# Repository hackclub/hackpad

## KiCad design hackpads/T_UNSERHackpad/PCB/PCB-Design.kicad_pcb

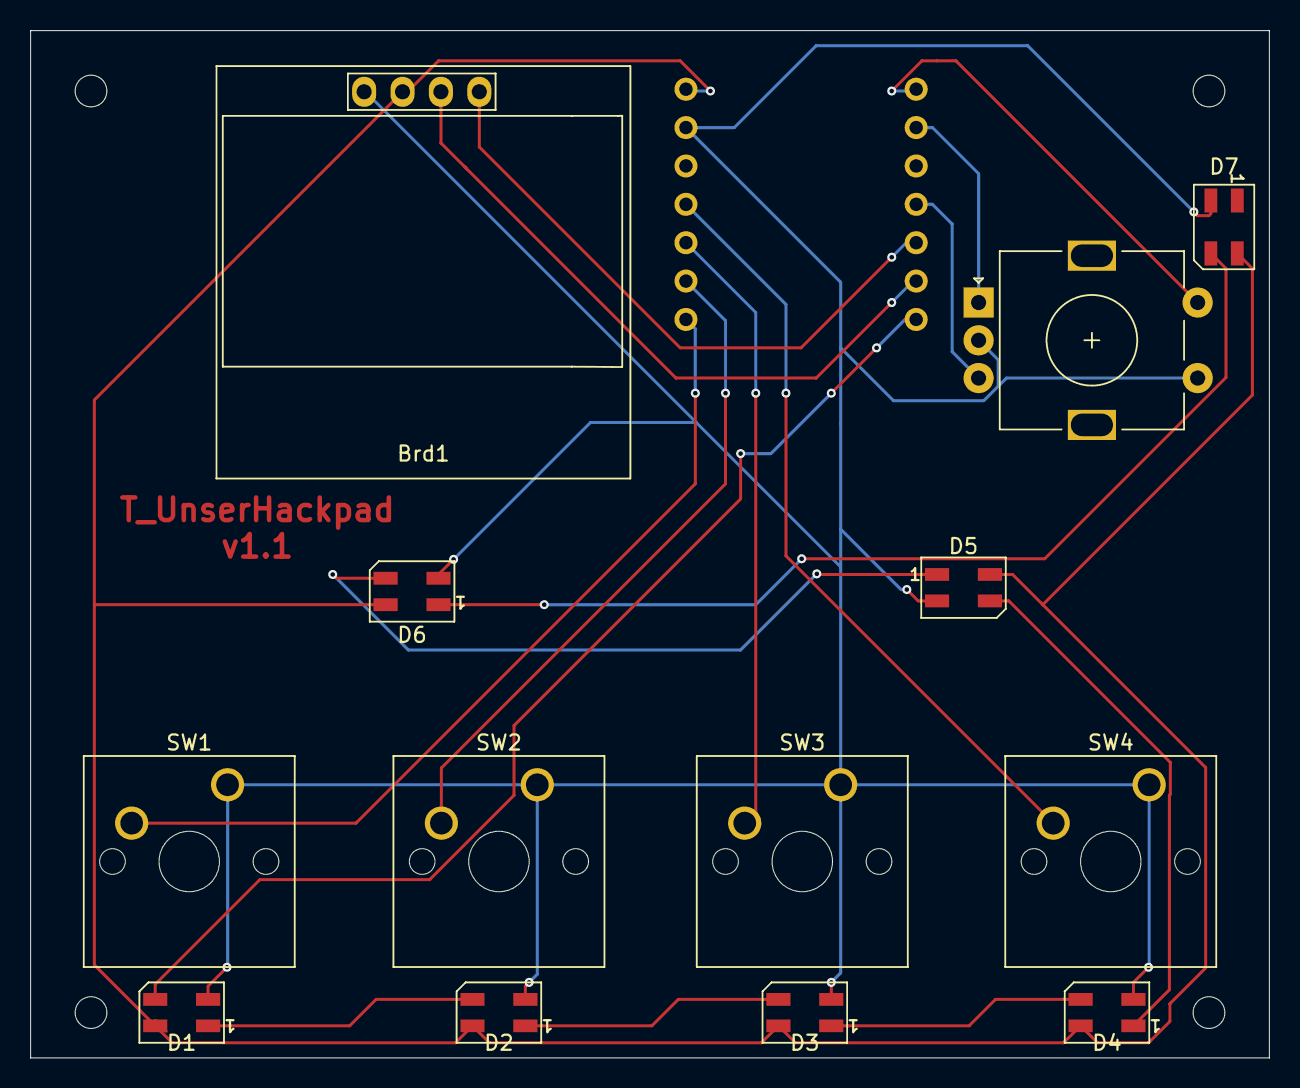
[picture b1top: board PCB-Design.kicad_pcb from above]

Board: 2 copper layers, 82.0 x 68.0 mm, 14 parts (1 on the bottom side), 18 nets.

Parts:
Brd1: SSD1306; 128x64OLED
D1, D2, D3, D4, D5, D6, D7: SK6812MINI; LED_SK6812MINI_PLCC4_3.5x3.5mm_P1.75mm
SW1, SW2, SW3, SW4: SW_Push; SW_Cherry_MX_1.00u_PCB
SW5: RotaryEncoder_Switch; RotaryEncoder_Alps_EC11E-Switch_Vertical_H20mm
U1: XIAO-RP2040-DIP

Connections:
+5V: Brd1.2 (VCC), D1.4 (VDD), D2.4 (VDD), D3.4 (VDD), D4.4 (VDD), D5.4 (VDD), D6.4 (VDD), D7.4 (VDD), U1.14 (VBUS)
GND: Brd1.1 (GND), D1.2 (VSS), D2.2 (VSS), D3.2 (VSS), D4.2 (VSS), D5.2 (VSS), D6.2 (VSS), D7.2 (VSS), SW1.1, SW2.1, SW3.1, SW4.1, SW5.C, SW5.S1, U1.13 (GND)
unnamed: Brd1.3 (SCL), U1.6 (GPIO7/SCL)
unnamed: Brd1.4 (SDA), U1.5 (GPIO6/SDA)
unnamed: D1.3 (DIN), U1.7 (GPIO0/TX)
unnamed: D1.1 (DOUT), D2.3 (DIN)
unnamed: D2.1 (DOUT), D3.3 (DIN)
unnamed: D3.1 (DOUT), D4.3 (DIN)
unnamed: D4.1 (DOUT), D5.3 (DIN)
unnamed: D5.1 (DOUT), D6.3 (DIN)
unnamed: D6.1 (DOUT), D7.3 (DIN)
unnamed: SW1.2, U1.8 (GPIO1/RX)
unnamed: SW2.2, U1.9 (GPIO2/SCK)
unnamed: SW4.2, U1.11 (GPIO3/MOSI)
unnamed: SW3.2, U1.10 (GPIO4/MISO)
unnamed: SW5.S2, U1.1 (GPIO26/ADC0/A0)
unnamed: SW5.A, U1.2 (GPIO27/ADC1/A1)
unnamed: SW5.B, U1.4 (GPIO29/ADC3/A3)

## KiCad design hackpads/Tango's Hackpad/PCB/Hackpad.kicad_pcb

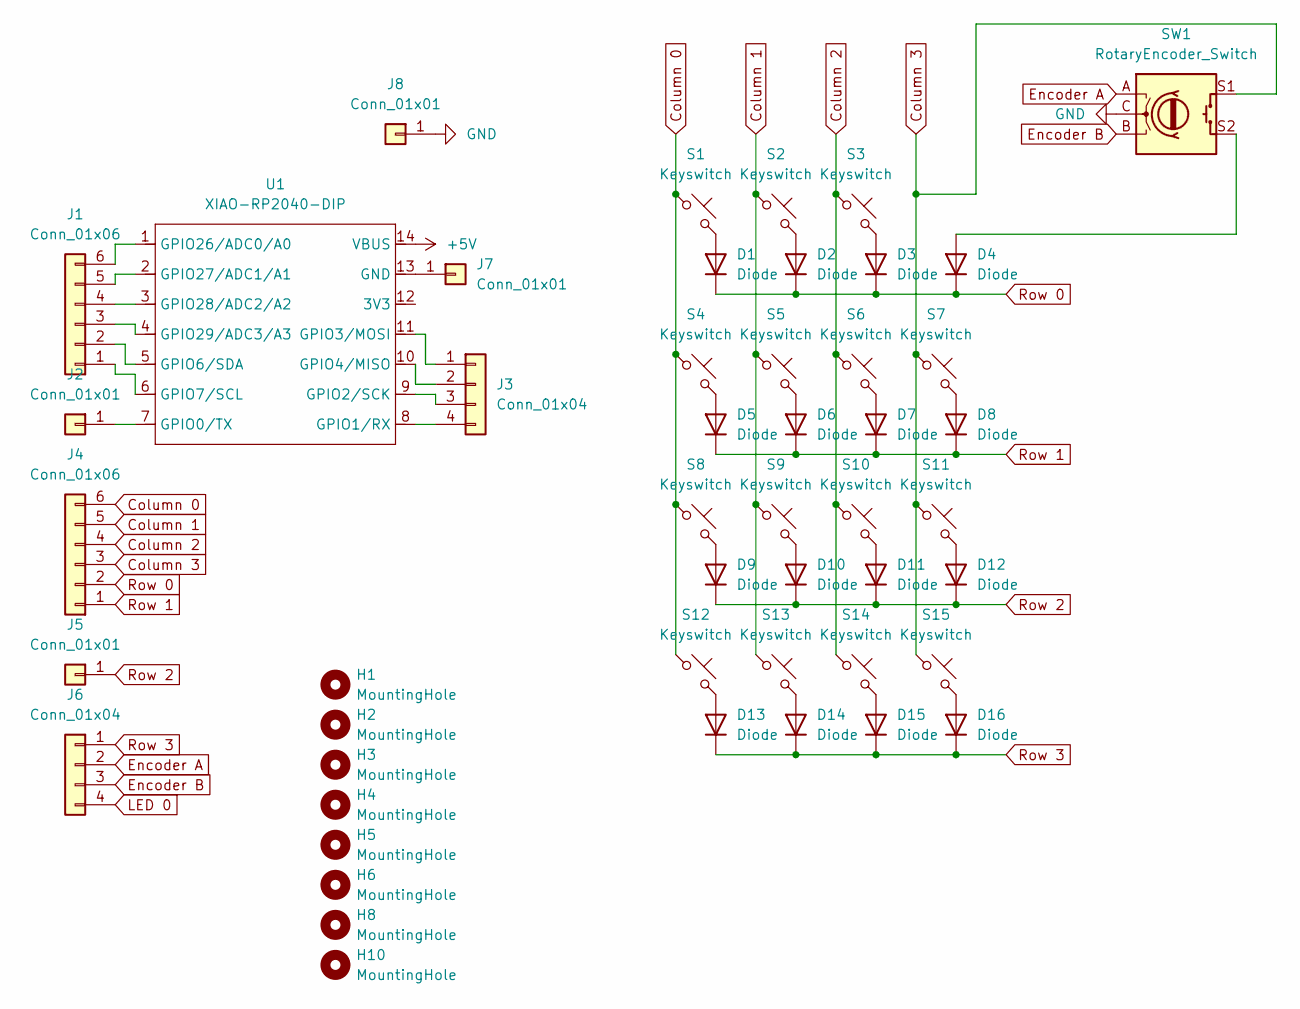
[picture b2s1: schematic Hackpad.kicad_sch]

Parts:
D1, D2, D3, D4, D5, D6, D7, D8, D9, D10, D11, D12, D13, D14, D15, D16: Diode; Diode_DO-35
H1, H2, H3, H4, H5, H6, H8, H10: MountingHole; MountingHole_2.2mm_M2_DIN965_Pad
J1, J4: Conn_01x06; SolderWire-0.1sqmm_1x06_P3.6mm_D0.4mm_OD1mm
J2, J5, J7, J8: Conn_01x01; SolderWire-0.1sqmm_1x01_D0.4mm_OD1mm
J3, J6: Conn_01x04; SolderWire-0.1sqmm_1x04_P3.6mm_D0.4mm_OD1mm
S1, S2, S3, S4, S5, S6, S7, S8, S9, S10, S11, S12, S13, S14, S15: Keyswitch; MX_PCB_1.00u
SW1: RotaryEncoder_Switch; RotaryEncoder_Alps_EC11E-Switch_Vertical_H20mm
U1: XIAO-RP2040-DIP

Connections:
+5V: U1.14 (VBUS)
Column 0: J4.6, S1.1, S4.1, S8.1, S12.1
Column 1: J4.5, S2.1, S5.1, S9.1, S13.1
Column 2: J4.4, S3.1, S6.1, S10.1, S14.1
Column 3: J4.3, S7.1, S11.1, S15.1, SW1.S1
Encoder A: J6.2, SW1.A
Encoder B: J6.3, SW1.B
GND: J8.1, SW1.C
LED 0: J6.4
unnamed: D1.2 (A), S1.2
unnamed: D2.2 (A), S2.2
unnamed: D3.2 (A), S3.2
unnamed: D4.2 (A), SW1.S2
unnamed: D5.2 (A), S4.2
unnamed: D6.2 (A), S5.2
unnamed: D7.2 (A), S6.2
unnamed: D8.2 (A), S7.2
unnamed: D9.2 (A), S8.2
unnamed: D10.2 (A), S9.2
unnamed: D11.2 (A), S10.2
unnamed: D12.2 (A), S11.2
unnamed: D13.2 (A), S12.2
unnamed: D14.2 (A), S13.2
unnamed: D15.2 (A), S14.2
unnamed: D16.2 (A), S15.2
unnamed: J1.1, U1.6 (GPIO7/SCL)
unnamed: J1.2, U1.5 (GPIO6/SDA)
unnamed: J1.3, U1.4 (GPIO29/ADC3/A3)
unnamed: J1.4, U1.3 (GPIO28/ADC2/A2)
unnamed: J1.5, U1.2 (GPIO27/ADC1/A1)
unnamed: J1.6, U1.1 (GPIO26/ADC0/A0)
unnamed: J2.1, U1.7 (GPIO0/TX)
unnamed: J3.1, U1.11 (GPIO3/MOSI)
unnamed: J3.2, U1.10 (GPIO4/MISO)
unnamed: J3.3, U1.9 (GPIO2/SCK)
unnamed: J3.4, U1.8 (GPIO1/RX)
unnamed: J7.1, U1.13 (GND)
Row 0: D1.1 (K), D2.1 (K), D3.1 (K), D4.1 (K), J4.2
Row 1: D5.1 (K), D6.1 (K), D7.1 (K), D8.1 (K), J4.1
Row 2: D9.1 (K), D10.1 (K), D11.1 (K), D12.1 (K), J5.1
Row 3: D13.1 (K), D14.1 (K), D15.1 (K), D16.1 (K), J6.1

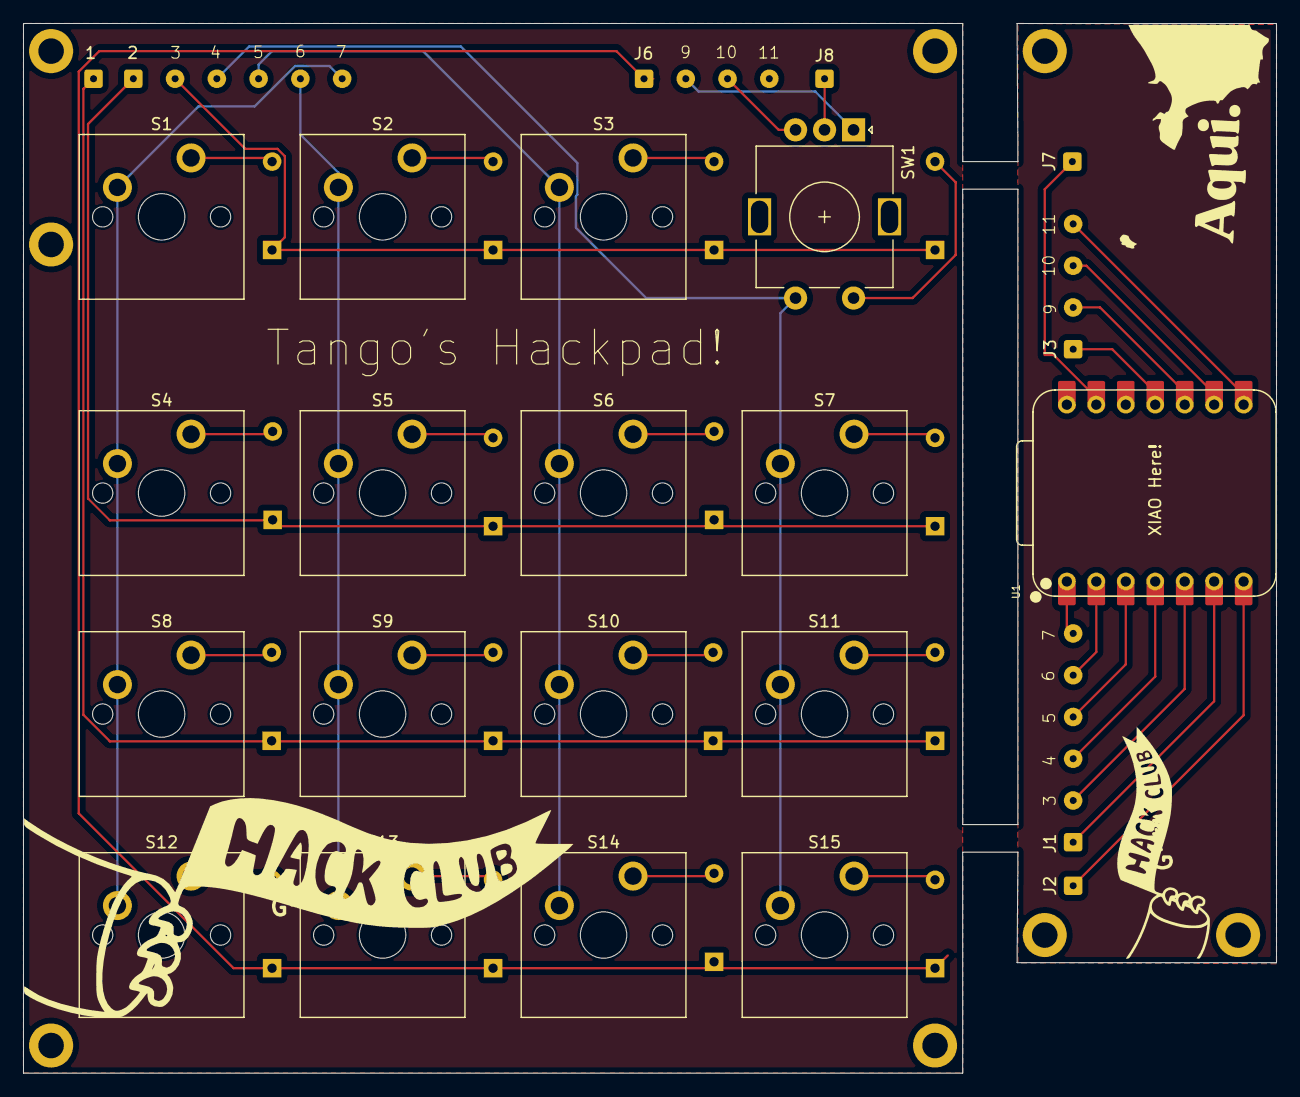
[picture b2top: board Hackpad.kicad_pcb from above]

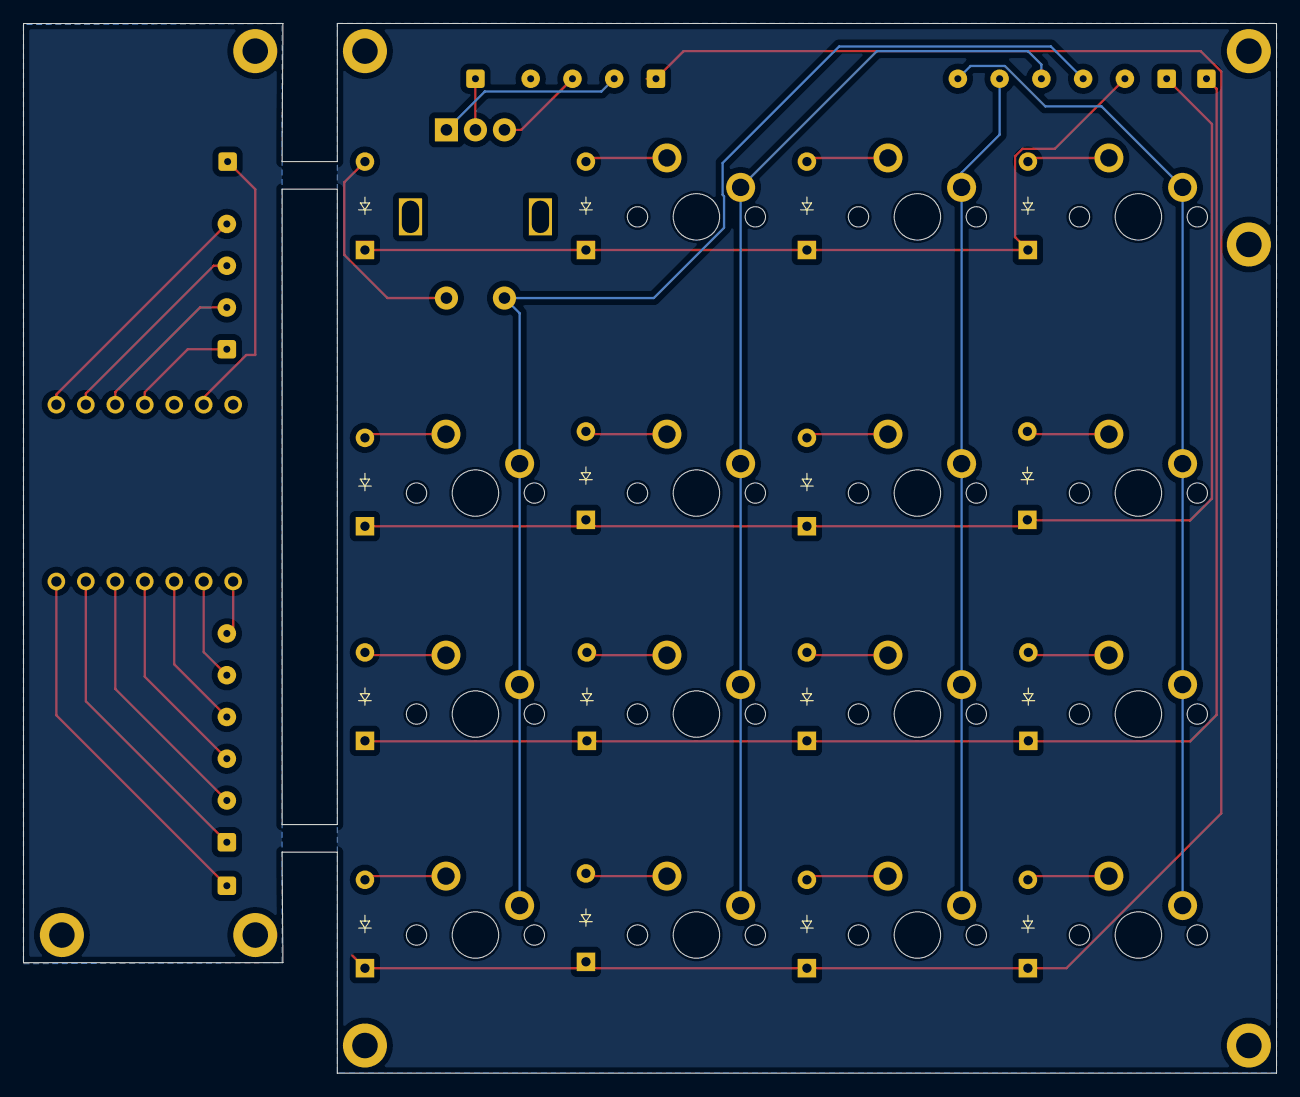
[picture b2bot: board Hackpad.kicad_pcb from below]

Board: 2 copper layers, 108.0 x 90.5 mm, 49 parts (16 on the bottom side), 39 nets.

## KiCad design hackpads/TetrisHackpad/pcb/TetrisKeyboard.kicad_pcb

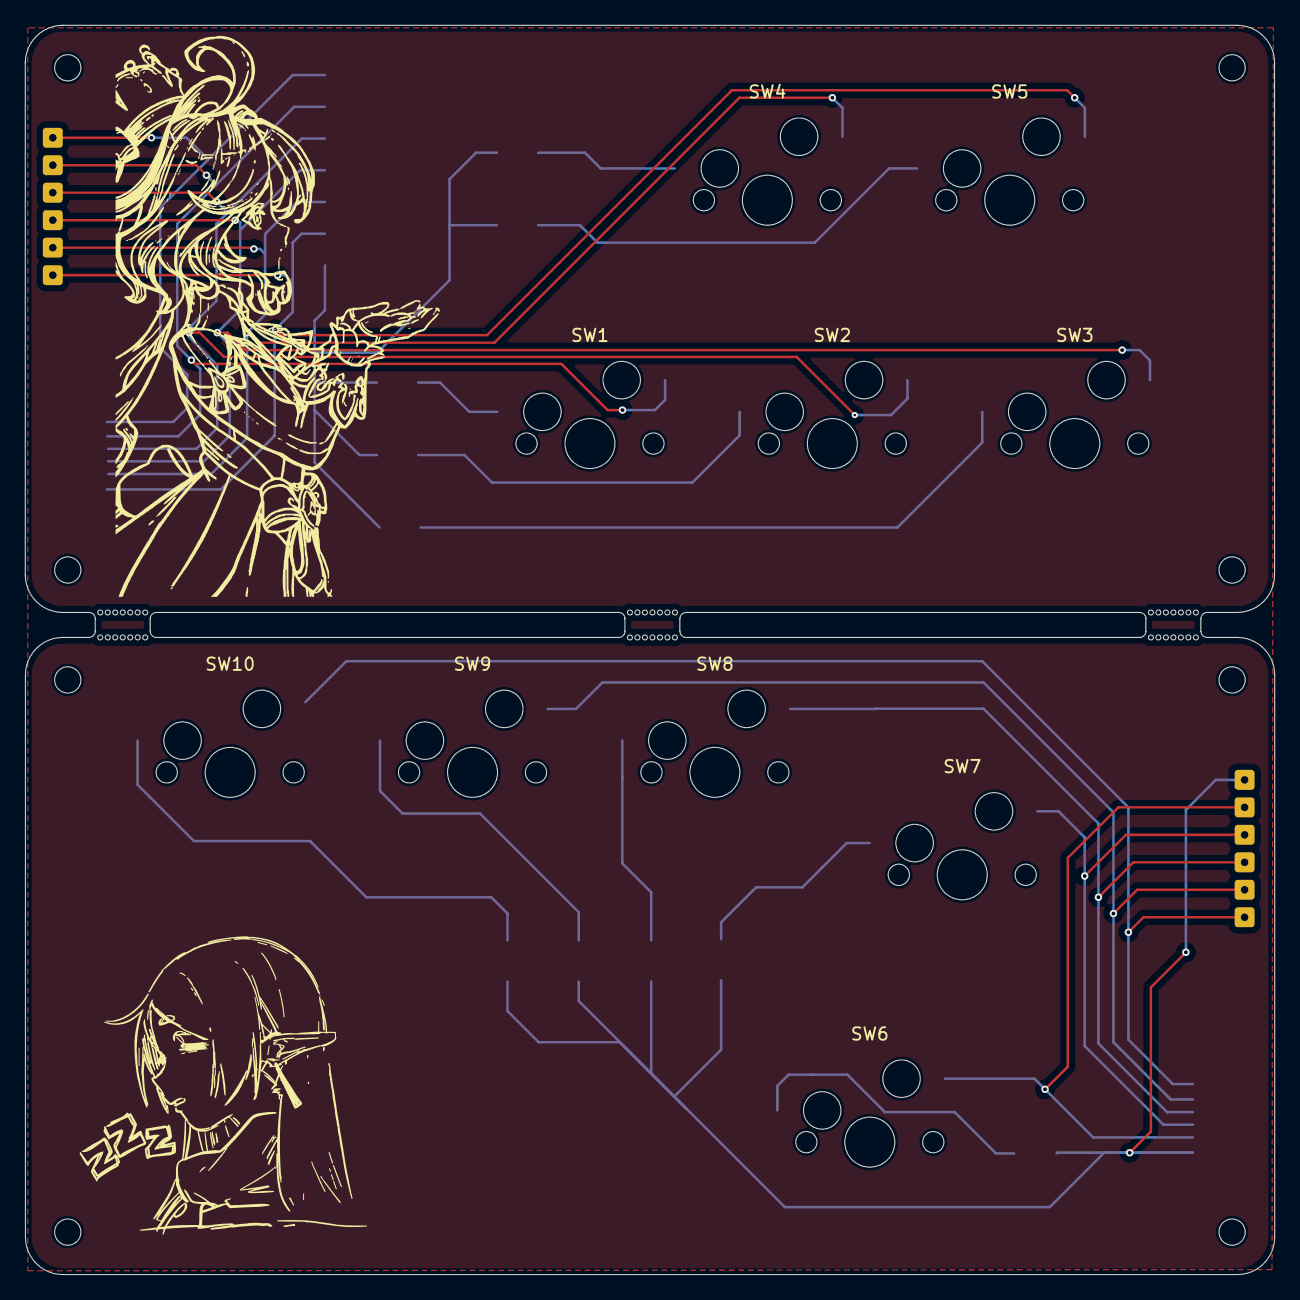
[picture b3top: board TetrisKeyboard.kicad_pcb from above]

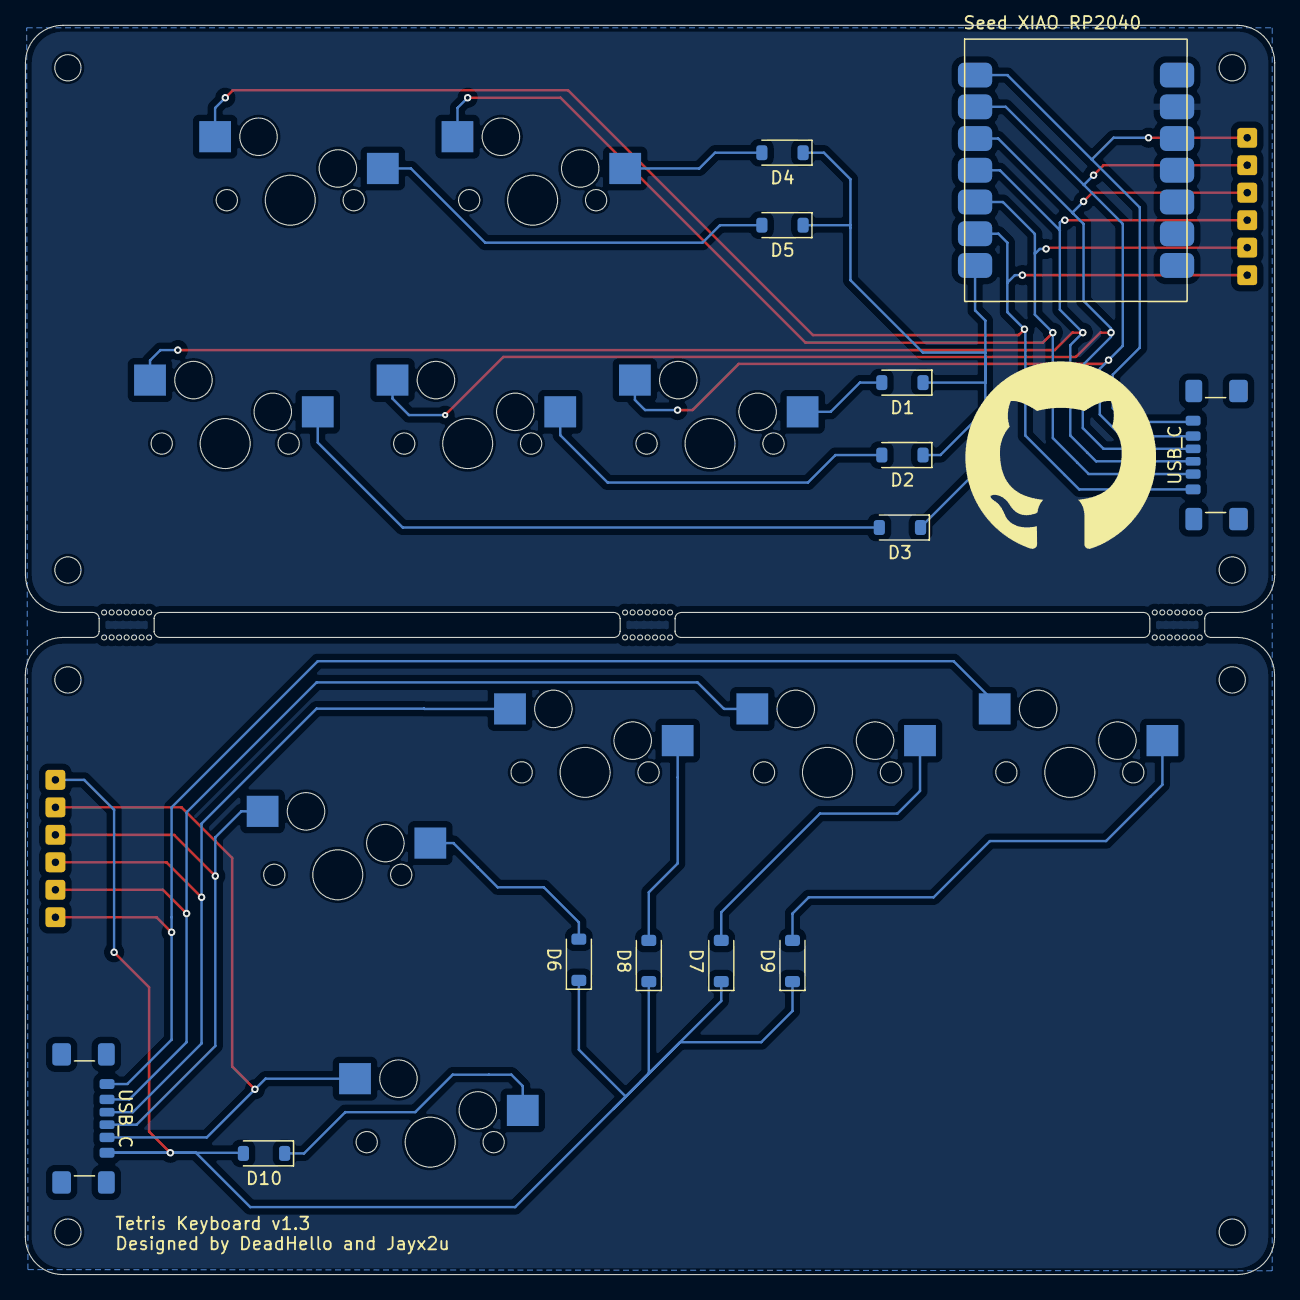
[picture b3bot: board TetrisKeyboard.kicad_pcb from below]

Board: 2 copper layers, 100.0 x 100.0 mm, 30 parts (13 on the bottom side), 13 nets.

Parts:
2.1mm, 2.1mm#2, 2.1mm#3, 2.1mm#4, 2.1mm#5, 2.1mm#6: MountingHole_2.1mm
D1, D2, D3, D4, D5, D6, D7, D8, D9, D10: 1N4148W; D_SOD-123
NO: LOGO
SW1, SW2, SW3, SW4, SW5, SW6, SW7, SW8, SW9, SW10: CherryMX_1.00u_KailhSocket
Seed XIAO RP2040: MOUDLE14P-SMD-2.54-21X17.8MM
USB_C: USB_C_Receptacle_GCT_USB4135-GF-A_6P_TopMnt_Horiz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; USB_C_Receptacle_GCT_USB4135-GF-A_6P_TopMnt_Horizontal
USB_C#2: USB_C_Receptacle_GCT_USB4135-GF-A_6P_TopMnt_Horiz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; USB_C_Receptacle_GCT_USB4135-GF-A_6P_TopMnt_Horizontal

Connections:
Col1: SW1.2, Seed XIAO RP2040.2, USB_C.A9
Col1-B: SW6.2, USB_C#2.A9
Col2: SW2.2, Seed XIAO RP2040.3, USB_C.B5
Col2-B: SW7.2, USB_C#2.B5
Col3: SW3.2, Seed XIAO RP2040.4, USB_C.A5
Col3-B: SW8.2, USB_C#2.A5
Col4: SW4.2, Seed XIAO RP2040.5, USB_C.B9
Col4-B: SW9.2, USB_C#2.B9
Col5: SW5.2, Seed XIAO RP2040.6, USB_C.B12
Col5-B: SW10.2, USB_C#2.B12
Row1: D1.1, D1.2, D2.1, D2.2, D3.1, D3.2, D4.1, D4.2, D5.1, D5.2, SW1.1, SW2.1, SW3.1, SW4.1, SW5.1, Seed XIAO RP2040.7
Row2: Seed XIAO RP2040.1, USB_C.A12
Row2-B: D6.1, D6.2, D7.1, D7.2, D8.1, D8.2, D9.1, D9.2, D10.1, D10.2, SW6.1, SW7.1, SW8.1, SW9.1, SW10.1, USB_C#2.A12

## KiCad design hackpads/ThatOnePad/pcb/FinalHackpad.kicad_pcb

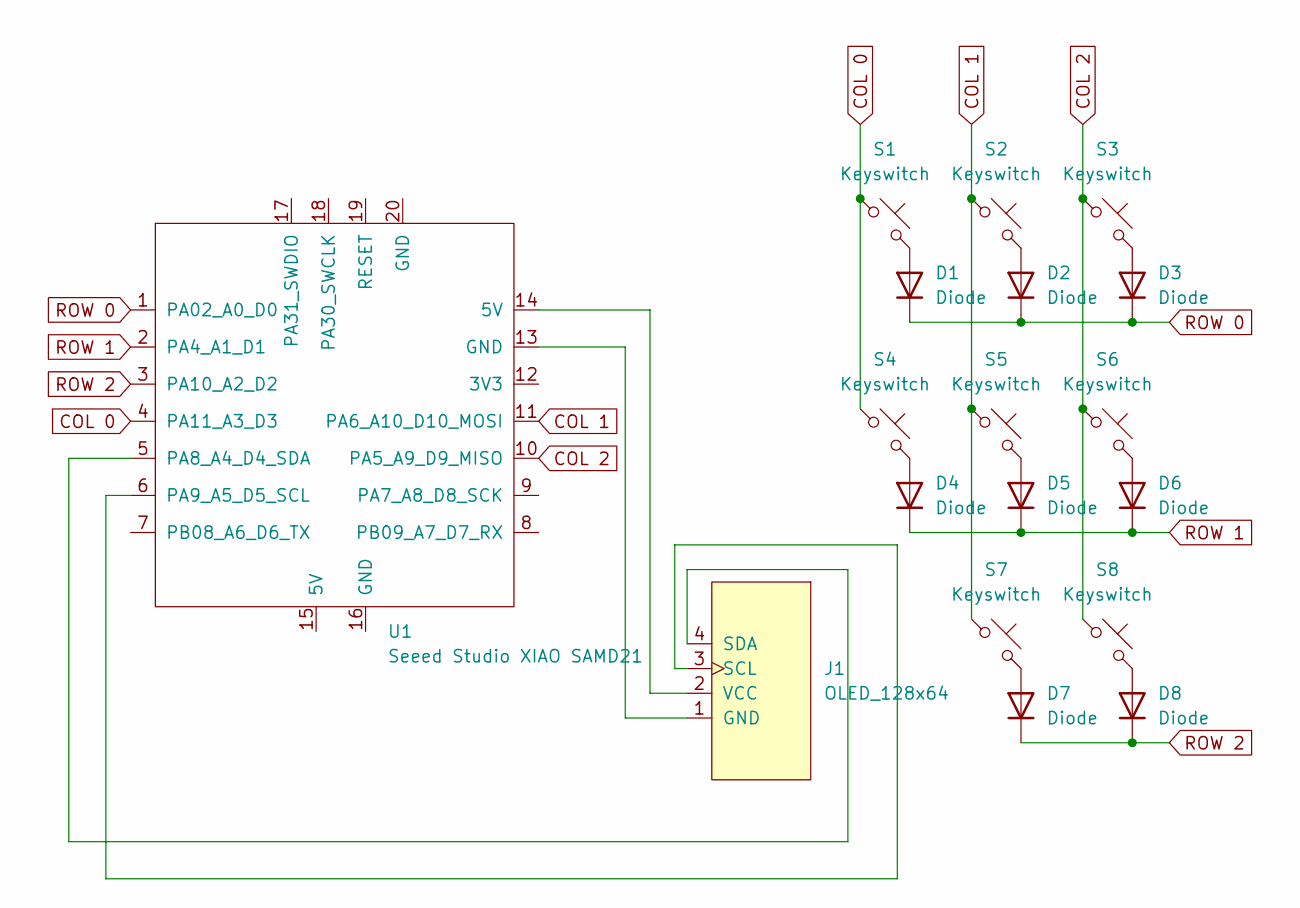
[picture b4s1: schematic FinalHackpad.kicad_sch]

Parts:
D1, D2, D3, D4, D5, D6, D7, D8: Diode; Diode_DO-35
J1: OLED_128x64
S1, S2, S3, S4, S5, S6, S7, S8: Keyswitch; SW_Cherry_MX_1.00u_PCB
U1: Seeed Studio XIAO SAMD21; Seeed_XIAO_RP2040

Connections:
COL 0: S1.1, S4.1, U1.4 (PA11_A3_D3)
COL 1: S2.1, S5.1, S7.1, U1.11 (PA6_A10_D10_MOSI)
COL 2: S3.1, S6.1, S8.1, U1.10 (PA5_A9_D9_MISO)
unnamed: D1.2 (A), S1.2
unnamed: D2.2 (A), S2.2
unnamed: D3.2 (A), S3.2
unnamed: D4.2 (A), S4.2
unnamed: D5.2 (A), S5.2
unnamed: D6.2 (A), S6.2
unnamed: D7.2 (A), S7.2
unnamed: D8.2 (A), S8.2
unnamed: J1.1 (GND), U1.13 (GND)
unnamed: J1.3 (SCL), U1.6 (PA9_A5_D5_SCL)
unnamed: J1.4 (SDA), U1.5 (PA8_A4_D4_SDA)
unnamed: J1.2 (VCC), U1.14 (5V)
ROW 0: D1.1 (K), D2.1 (K), D3.1 (K), U1.1 (PA02_A0_D0)
ROW 1: D4.1 (K), D5.1 (K), D6.1 (K), U1.2 (PA4_A1_D1)
ROW 2: D7.1 (K), D8.1 (K), U1.3 (PA10_A2_D2)

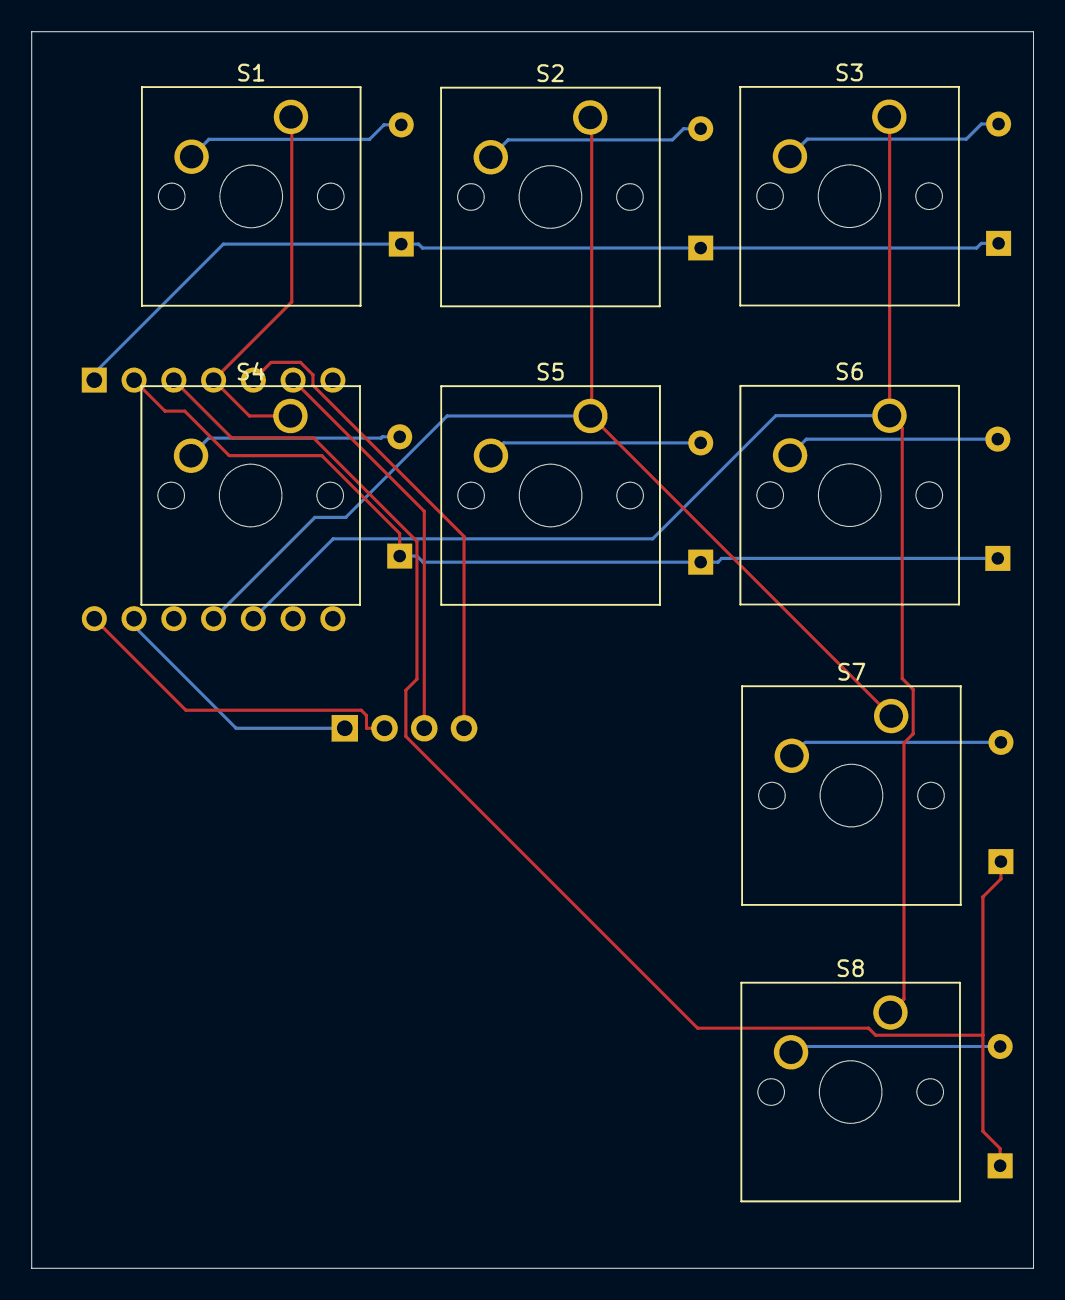
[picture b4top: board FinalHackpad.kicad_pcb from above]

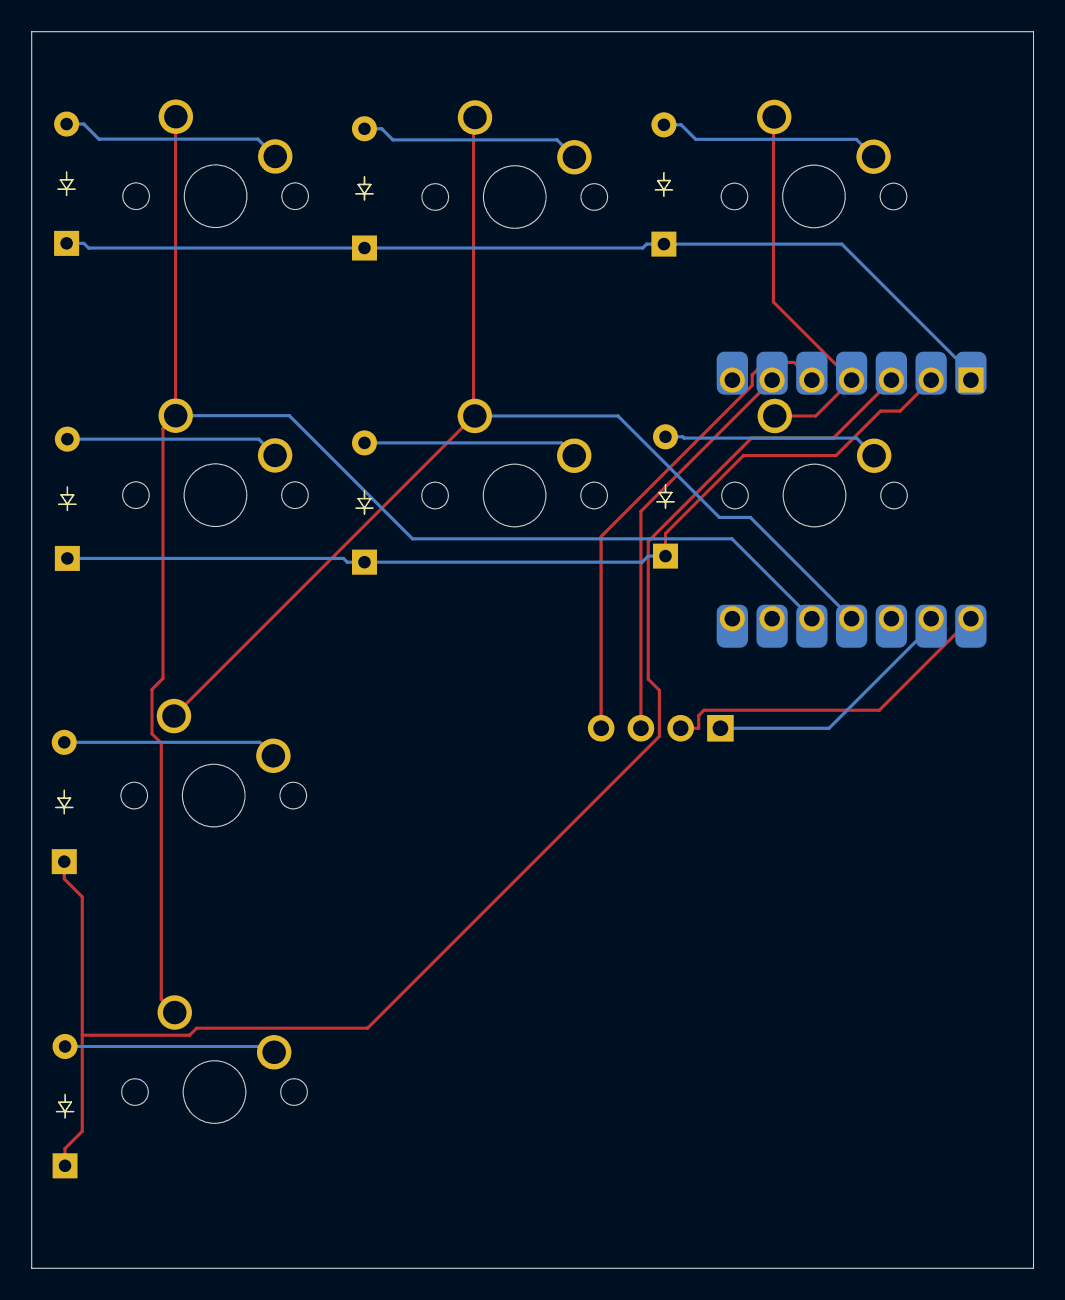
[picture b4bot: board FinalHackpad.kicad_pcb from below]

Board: 2 copper layers, 64.0 x 79.0 mm, 18 parts (9 on the bottom side), 18 nets.

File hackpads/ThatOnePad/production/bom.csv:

Designator,Footprint,Quantity,Value,LCSC Part #
"D1, D2, D3, D4, D5, D6, D7, D8",Diode_DO-35,8,Diode,
J1,OLED_128x64,1,OLED_128x64,
"S1, S2, S3, S4, S5, S6, S7, S8",SW_Cherry_MX_1.00u_PCB,8,Keyswitch,
U1,Seeed_XIAO_RP2040,1,Seeed Studio XIAO SAMD21,

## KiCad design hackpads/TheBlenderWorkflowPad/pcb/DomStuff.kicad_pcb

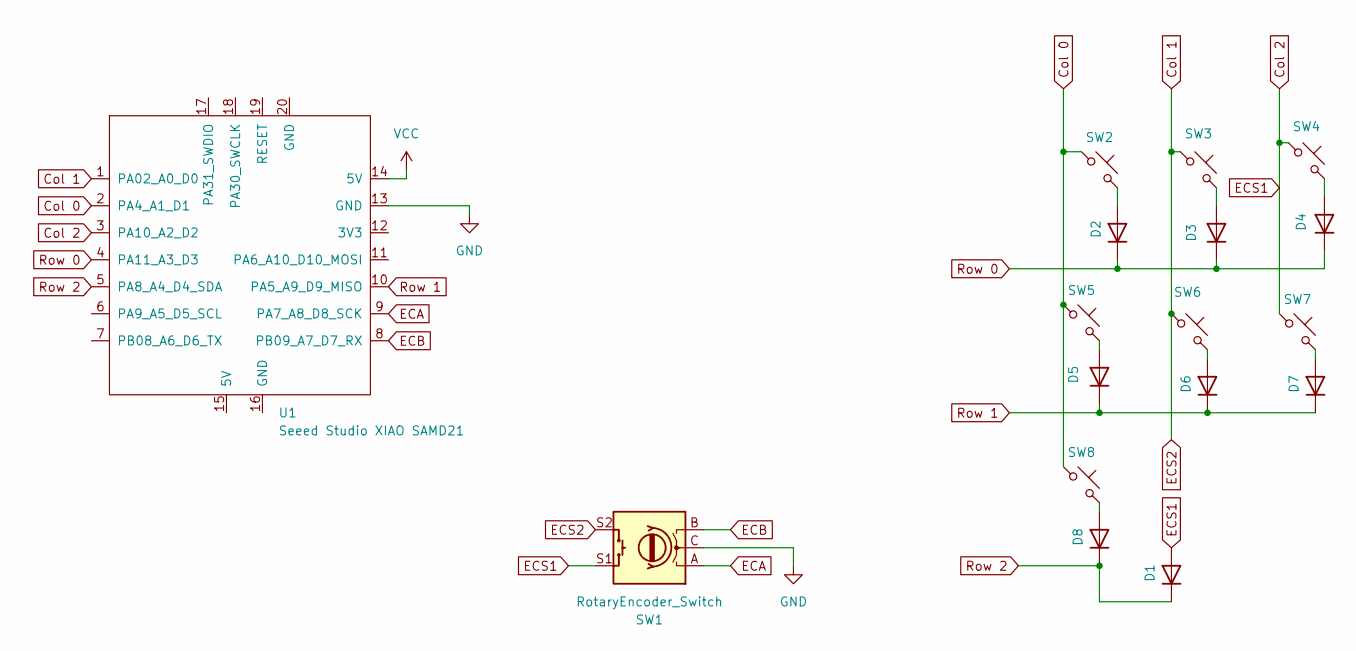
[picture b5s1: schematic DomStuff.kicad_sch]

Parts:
D1, D2, D3, D4, D5, D6, D7, D8: 1N4148WT; D_DO-35_SOD27_P7.62mm_Horizontal
SW1: RotaryEncoder_Switch; RotaryEncoder_Alps_EC11E-Switch_Vertical_H20mm
SW2, SW3, SW4, SW5, SW6, SW7, SW8: SW_Push_45deg; SW_Cherry_MX_1.00u_PCB
U1: Seeed Studio XIAO SAMD21; XIAO-Generic-Thruhole-14P-2.54-21X17.8MM

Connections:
Col 0: SW2.1, SW5.1, SW8.1, U1.2 (PA4_A1_D1)
Col 1: SW1.S2, SW3.1, SW6.1, U1.1 (PA02_A0_D0)
Col 2: D1.2 (A), SW1.S1, SW4.1, SW7.1, U1.3 (PA10_A2_D2)
ECA: SW1.A, U1.9 (PA7_A8_D8_SCK)
ECB: SW1.B, U1.8 (PB09_A7_D7_RX)
GND: SW1.C, U1.13 (GND)
unnamed: D2.2 (A), SW2.2
unnamed: D3.2 (A), SW3.2
unnamed: D4.2 (A), SW4.2
unnamed: D5.2 (A), SW5.2
unnamed: D6.2 (A), SW6.2
unnamed: D7.2 (A), SW7.2
unnamed: D8.2 (A), SW8.2
Row 0: D2.1 (K), D3.1 (K), D4.1 (K), U1.4 (PA11_A3_D3)
Row 1: D5.1 (K), D6.1 (K), D7.1 (K), U1.10 (PA5_A9_D9_MISO)
Row 2: D1.1 (K), D8.1 (K), U1.5 (PA8_A4_D4_SDA)
VCC: U1.14 (5V)

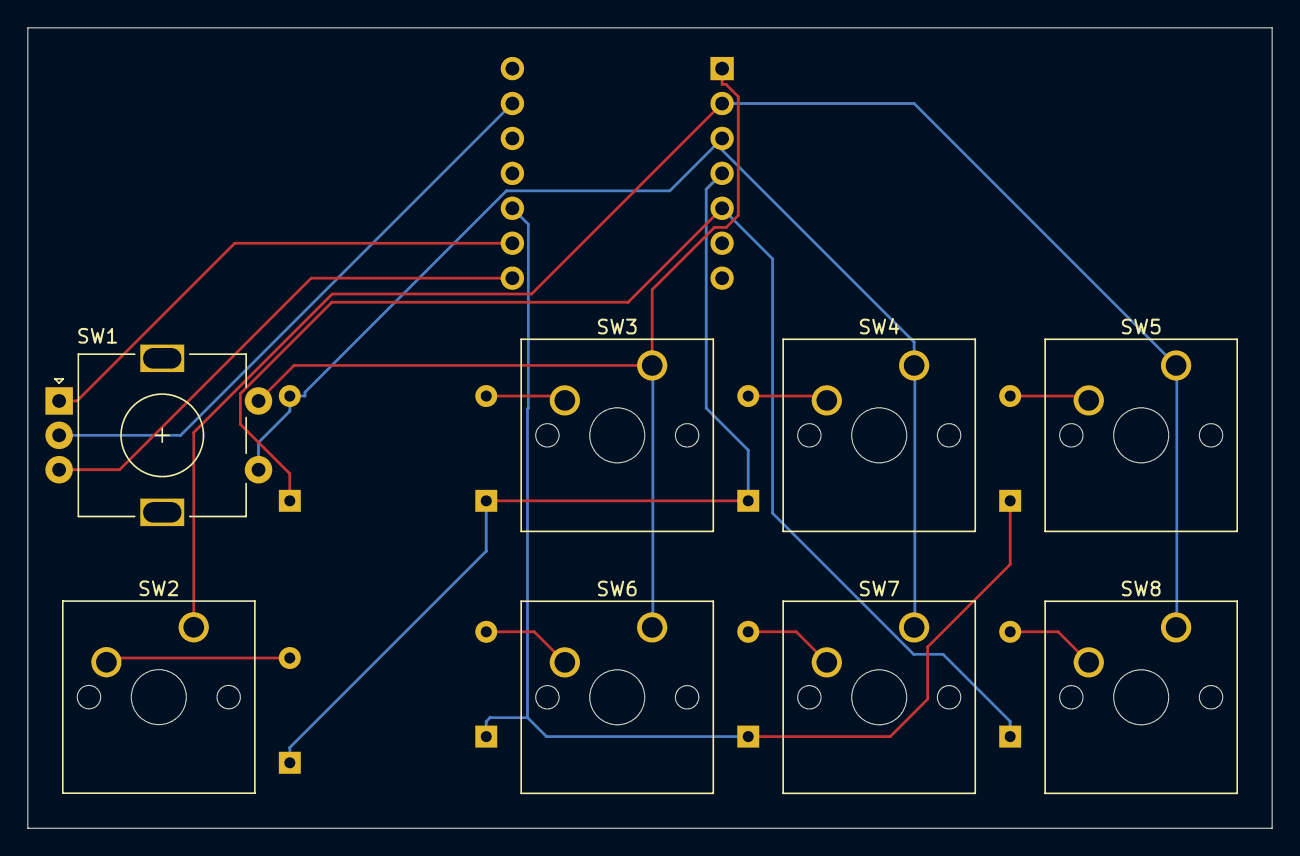
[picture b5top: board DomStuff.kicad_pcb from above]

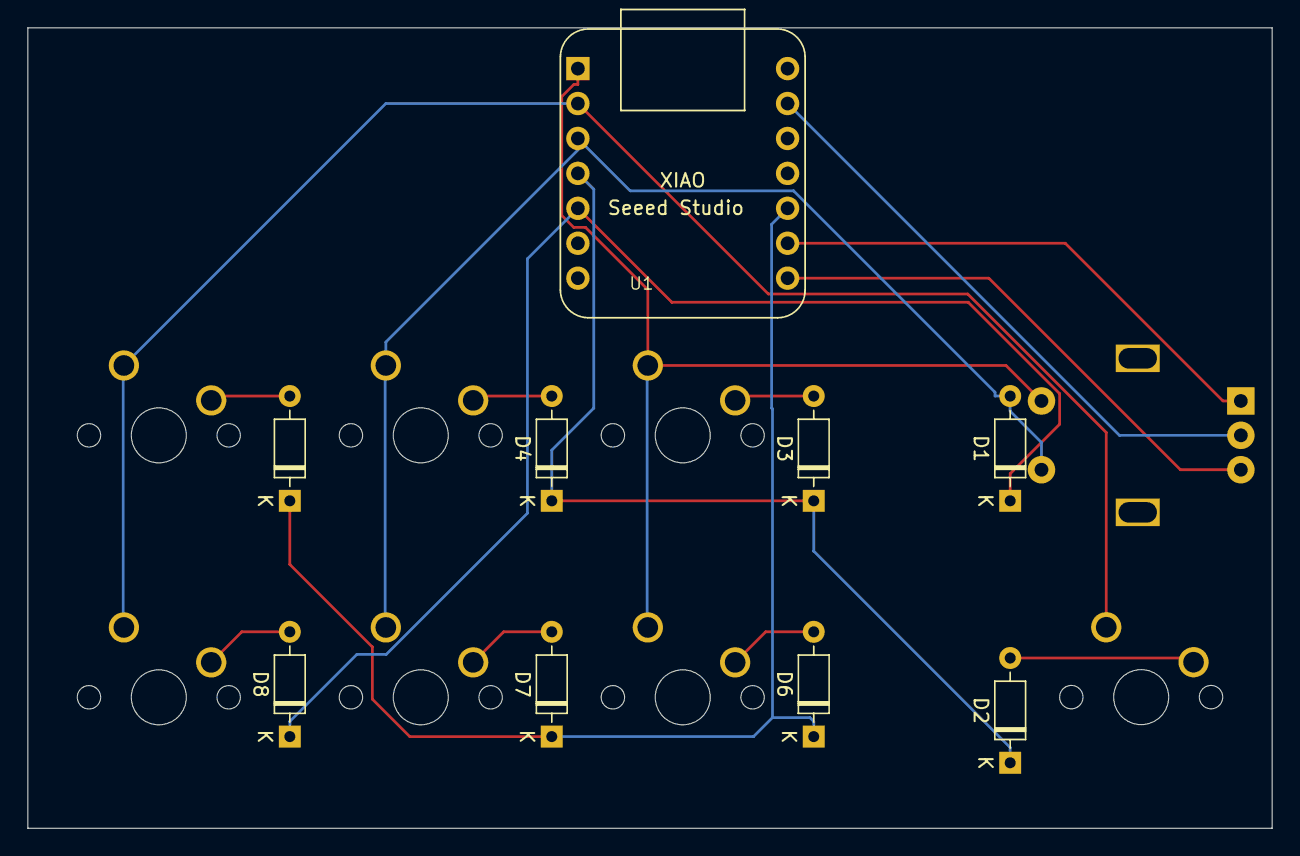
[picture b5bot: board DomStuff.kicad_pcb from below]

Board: 2 copper layers, 90.5 x 58.2 mm, 17 parts (9 on the bottom side), 16 nets.
